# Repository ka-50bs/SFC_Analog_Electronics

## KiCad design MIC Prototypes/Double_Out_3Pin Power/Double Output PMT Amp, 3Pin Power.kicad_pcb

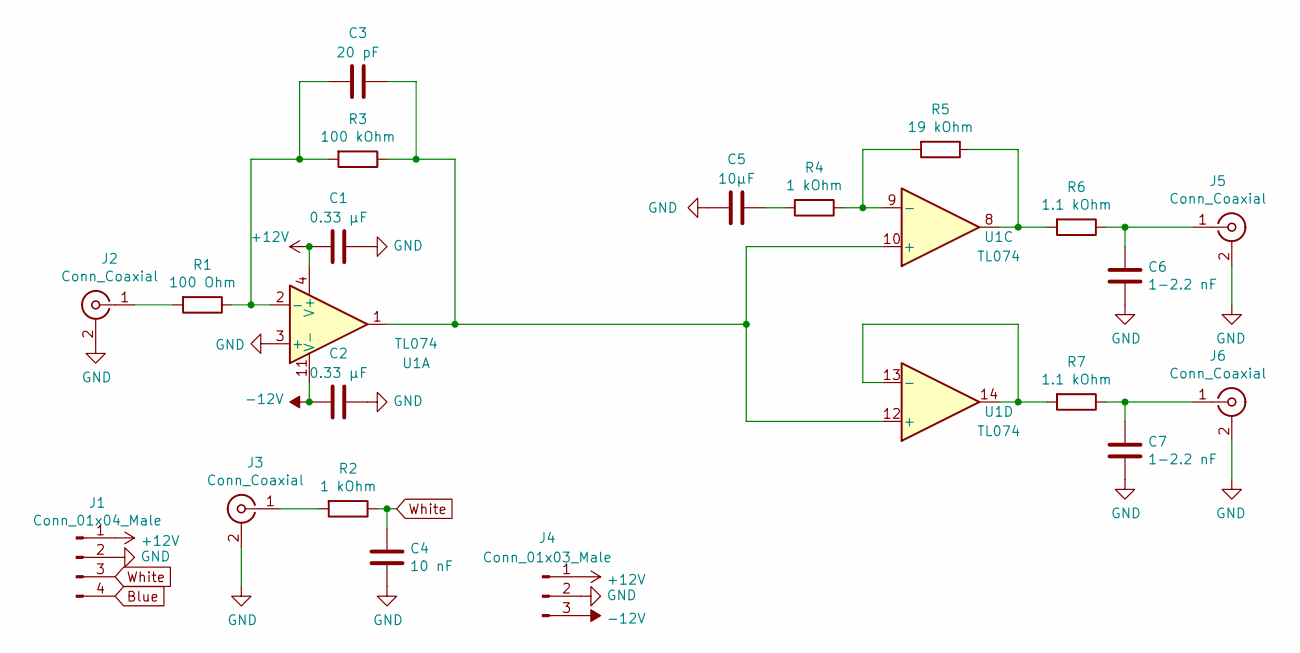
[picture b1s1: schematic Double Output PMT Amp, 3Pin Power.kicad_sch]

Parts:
C1, C2: 0.33 μF; C_1206_3216Metric_Pad1.33x1.80mm_HandSolder
C3: 20 pF; C_1206_3216Metric_Pad1.33x1.80mm_HandSolder
C4: 10 nF; C_1206_3216Metric_Pad1.33x1.80mm_HandSolder
C5: 10μF; C_1206_3216Metric_Pad1.33x1.80mm_HandSolder
C6, C7: 1-2.2 nF; C_1206_3216Metric_Pad1.33x1.80mm_HandSolder
J1: Conn_01x04_Male; PinHeader_1x04_P2.54mm_Vertical
J2, J3, J5, J6: Conn_Coaxial; SMA_Amphenol_132291-12_Vertical
J4: Conn_01x03_Male; Molex_KK-254_AE-6410-03A_1x03_P2.54mm_Vertical
R1: 100 Ohm; R_1206_3216Metric_Pad1.30x1.75mm_HandSolder
R2, R4: 1 kOhm; R_1206_3216Metric_Pad1.30x1.75mm_HandSolder
R3: 100 kOhm; R_1206_3216Metric_Pad1.30x1.75mm_HandSolder
R5: 19 kOhm; R_1206_3216Metric_Pad1.30x1.75mm_HandSolder
R6, R7: 1.1 kOhm; R_1206_3216Metric_Pad1.30x1.75mm_HandSolder
U1: TL074; DIP-14_W7.62mm_LongPads

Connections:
+12V: C1.2, J1.1, J4.1, U1.4 (V+)
-12V: C2.2, J4.3, U1.11 (V-)
Blue: J1.4
GND: C1.1, C2.1, C4.2, C5.1, C6.2, C7.2, J1.2, J2.2 (Ext), J3.2 (Ext), J4.2, J5.2 (Ext), J6.2 (Ext), U1.3 (+)
unnamed: C3.1, R3.1, U1.1, U1.10 (+), U1.12 (+)
unnamed: C3.2, R1.1, R3.2, U1.2 (-)
unnamed: C5.2, R4.2
unnamed: C6.1, J5.1 (In), R6.1
unnamed: C7.1, J6.1 (In), R7.1
unnamed: J2.1 (In), R1.2
unnamed: J3.1 (In), R2.2
unnamed: R4.1, R5.2, U1.9 (-)
unnamed: R5.1, R6.2, U1.8
unnamed: R7.2, U1.13 (-), U1.14
White: C4.1, J1.3, R2.1

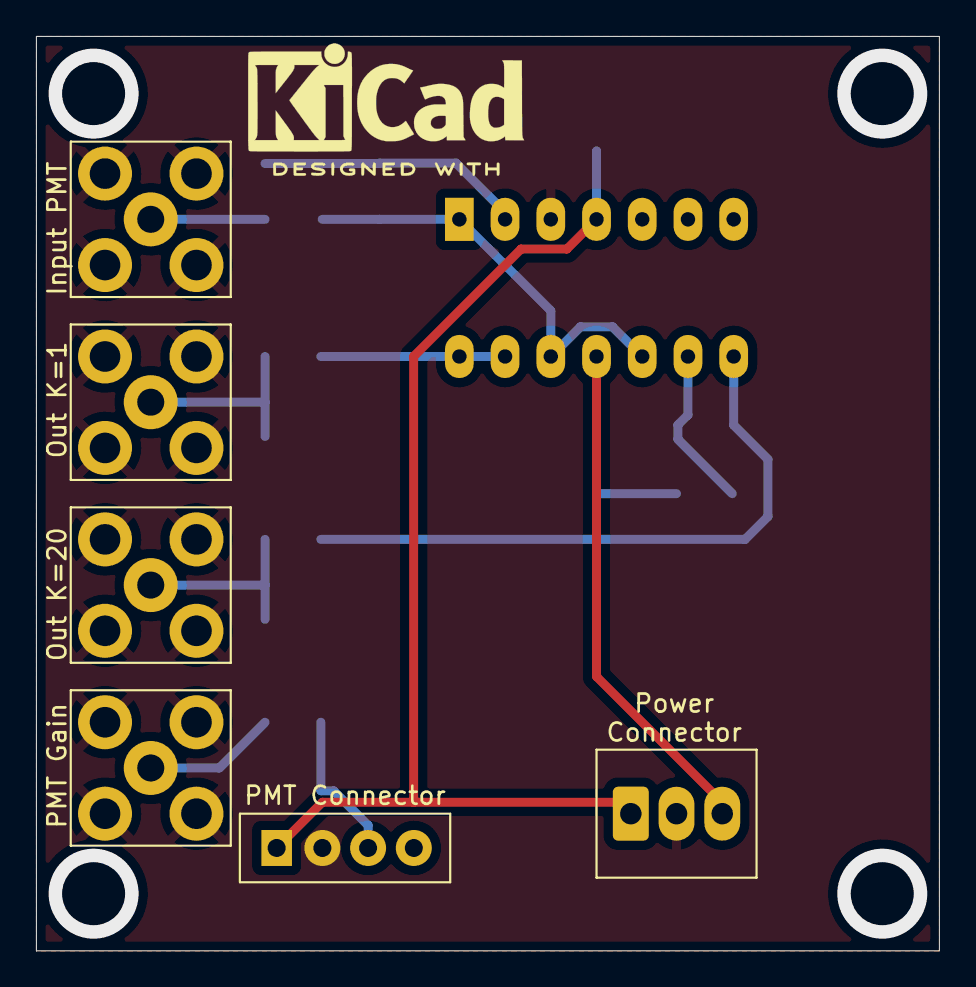
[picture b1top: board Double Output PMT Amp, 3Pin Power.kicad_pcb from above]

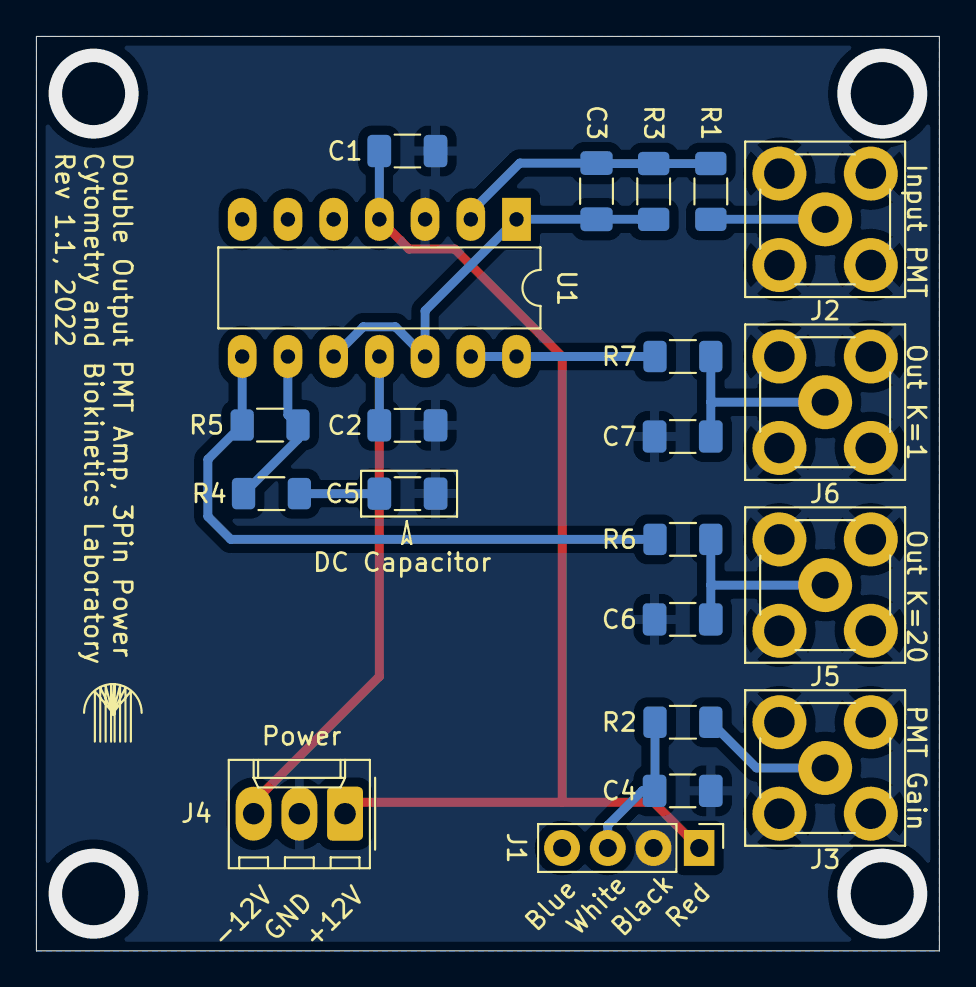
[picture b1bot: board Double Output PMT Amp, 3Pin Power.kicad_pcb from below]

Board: 2 copper layers, 50.2 x 50.8 mm, 21 parts (21 on the bottom side), 14 nets.

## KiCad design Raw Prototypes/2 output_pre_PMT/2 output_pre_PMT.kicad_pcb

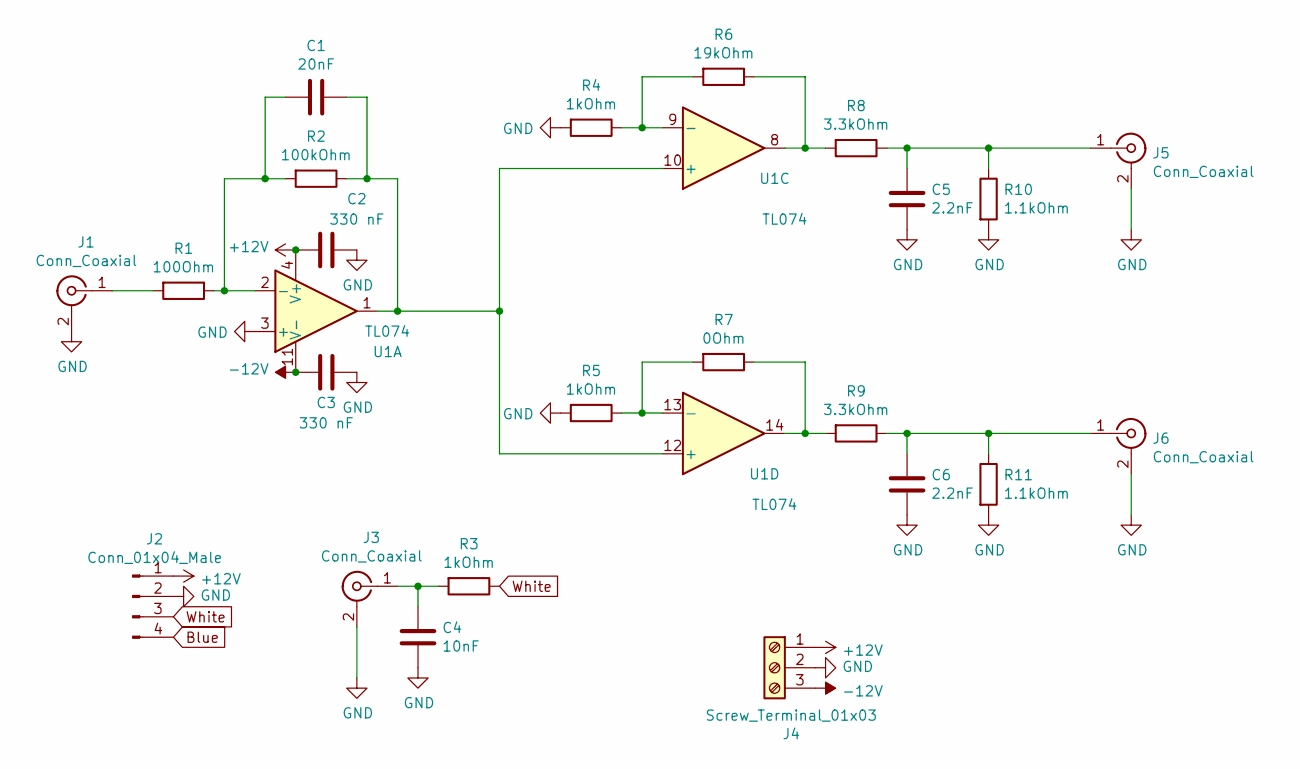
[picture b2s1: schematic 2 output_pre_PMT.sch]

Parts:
C1: 20nF; C_Disc_D7.5mm_W2.5mm_P5.00mm
C2, C3: 330 nF; C_Disc_D7.5mm_W2.5mm_P5.00mm
C4: 10nF; C_Disc_D7.5mm_W2.5mm_P5.00mm
C5, C6: 2.2nF; C_Disc_D7.5mm_W2.5mm_P5.00mm
J1, J3, J5, J6: Conn_Coaxial; SMA_Amphenol_132291-12_Vertical
J2: Conn_01x04_Male; PinHeader_1x04_P2.54mm_Vertical
J4: Screw_Terminal_01x03; TerminalBlock_Phoenix_MKDS-1,5-3_1x03_P5.00mm_Horizontal
R1: 100Ohm; R_Axial_DIN0207_L6.3mm_D2.5mm_P7.62mm_Horizontal
R2: 100kOhm; R_Axial_DIN0207_L6.3mm_D2.5mm_P7.62mm_Horizontal
R3, R4, R5: 1kOhm; R_Axial_DIN0207_L6.3mm_D2.5mm_P7.62mm_Horizontal
R6: 19kOhm; R_Axial_DIN0207_L6.3mm_D2.5mm_P7.62mm_Horizontal
R7: 0Ohm; R_Axial_DIN0207_L6.3mm_D2.5mm_P7.62mm_Horizontal
R8, R9: 3.3kOhm; R_Axial_DIN0207_L6.3mm_D2.5mm_P7.62mm_Horizontal
R10, R11: 1.1kOhm; R_Axial_DIN0207_L6.3mm_D2.5mm_P7.62mm_Horizontal
U1: TL074; DIP-14_W7.62mm_LongPads

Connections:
+12V: C2.2, J2.1, J4.1, U1.4 (V+)
-12V: C3.2, J4.3, U1.11 (V-)
Blue: J2.4
GND: C2.1, C3.1, C4.2, C5.2, C6.2, J1.2 (Ext), J2.2, J3.2 (Ext), J4.2, J5.2 (Ext), J6.2 (Ext), R4.2, R5.2, R10.2, R11.2, U1.3 (+)
unnamed: C1.1, R2.1, U1.1, U1.10 (+), U1.12 (+)
unnamed: C1.2, R1.1, R2.2, U1.2 (-)
unnamed: C4.1, J3.1 (In), R3.2
unnamed: C5.1, J5.1 (In), R8.1, R10.1
unnamed: C6.1, J6.1 (In), R9.1, R11.1
unnamed: J1.1 (In), R1.2
unnamed: R4.1, R6.2, U1.9 (-)
unnamed: R5.1, R7.2, U1.13 (-)
unnamed: R6.1, R8.2, U1.8
unnamed: R7.1, R9.2, U1.14
White: J2.3, R3.1

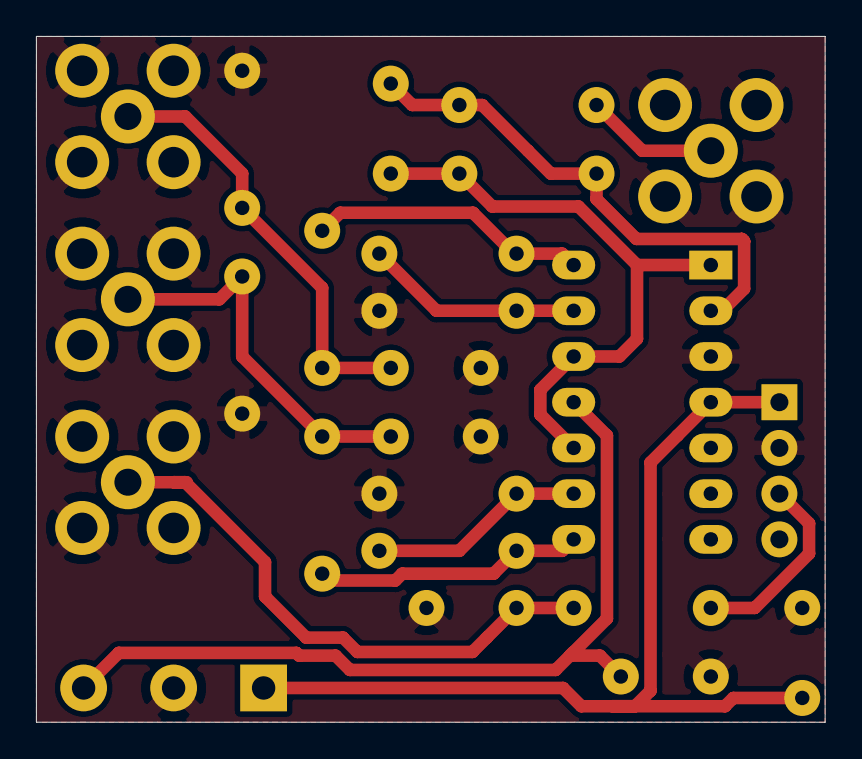
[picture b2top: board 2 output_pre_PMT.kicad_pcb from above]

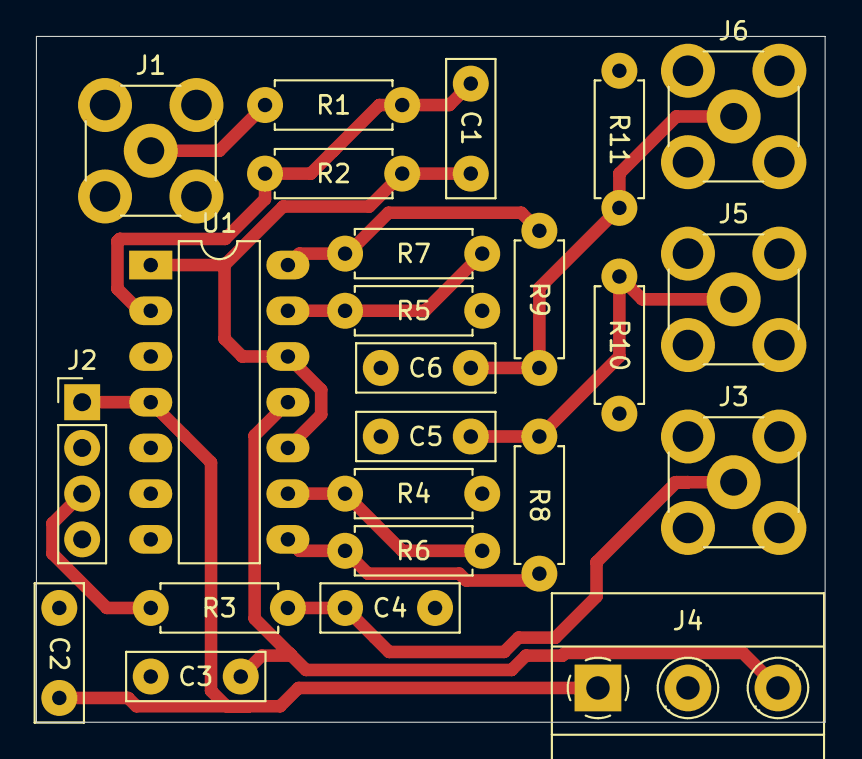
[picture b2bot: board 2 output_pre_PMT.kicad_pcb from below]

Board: 2 copper layers, 43.8 x 38.1 mm, 24 parts (24 on the bottom side), 14 nets.

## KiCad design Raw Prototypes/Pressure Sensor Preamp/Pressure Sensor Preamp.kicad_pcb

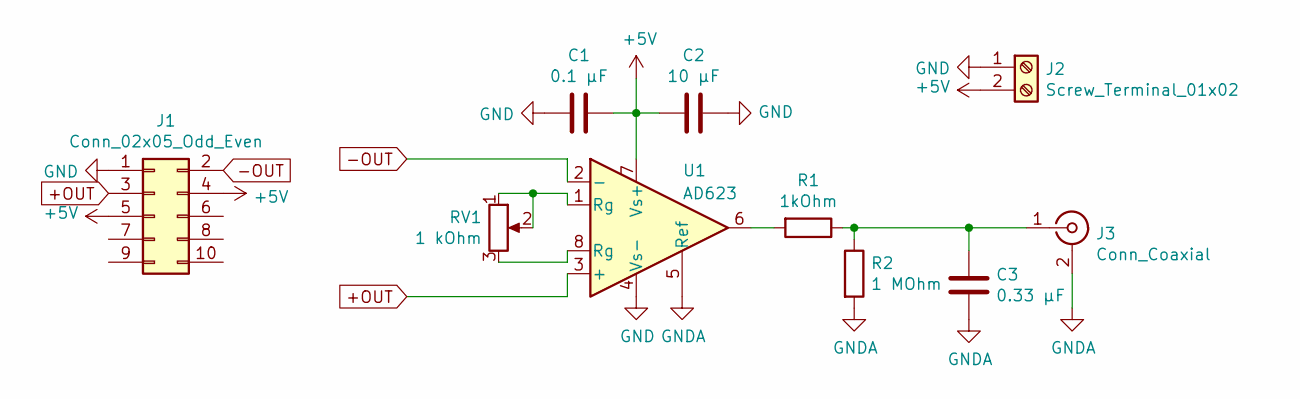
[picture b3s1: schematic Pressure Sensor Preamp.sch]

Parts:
C1: 0.1 μF; C_Disc_D9.0mm_W5.0mm_P7.50mm
C2: 10 μF; C_Disc_D9.0mm_W5.0mm_P7.50mm
C3: 0.33 μF; C_Disc_D9.0mm_W5.0mm_P7.50mm
J1: Conn_02x05_Odd_Even; IDC-Header_2x05_P2.54mm_Vertical
J2: Screw_Terminal_01x02; TerminalBlock_Phoenix_MKDS-1,5-2-5.08_1x02_P5.08mm_Horizont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
J3: Conn_Coaxial; SMA_Amphenol_132291-12_Vertical
R1: 1kOhm; R_Axial_DIN0207_L6.3mm_D2.5mm_P10.16mm_Horizontal
R2: 1 MOhm; R_Axial_DIN0207_L6.3mm_D2.5mm_P10.16mm_Horizontal
RV1: 1 kOhm; Potentiometer_Bourns_3266Y_Vertical
U1: AD623; DIP-8_W7.62mm_LongPads

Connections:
+5V: C1.1, C2.2, J1.4, J1.5, J2.2, U1.7 (Vs+)
+OUT: J1.3, U1.3 (+)
-OUT: J1.2, U1.2 (-)
GND: C1.2, C2.1, J1.1, J2.1, U1.4 (Vs-)
GNDA: C3.2, J3.2 (Ext), R2.2, U1.5 (Ref)
unnamed: C3.1, J3.1 (In), R1.1, R2.1
unnamed: R1.2, U1.6
unnamed: RV1.1, RV1.2, U1.1 (Rg)
unnamed: RV1.3, U1.8 (Rg)

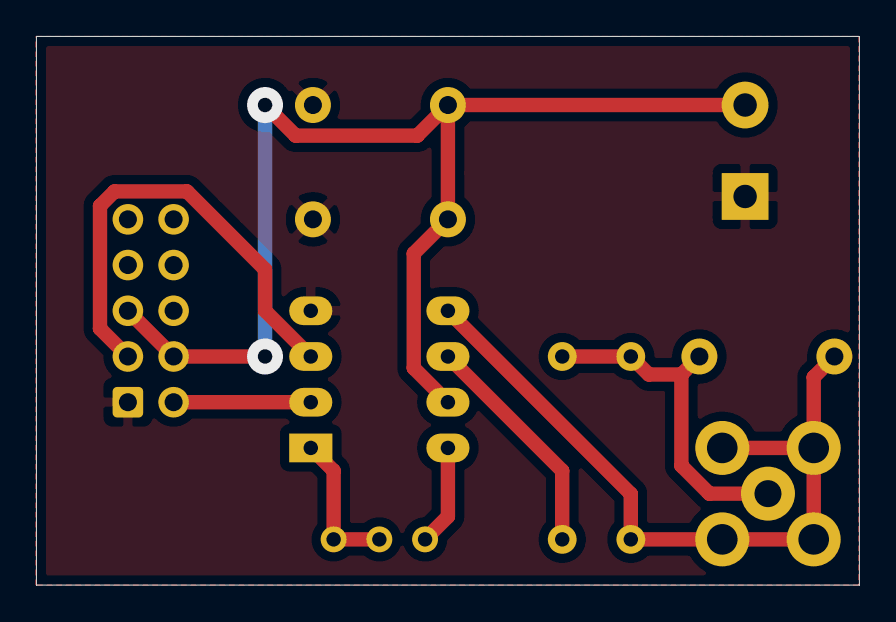
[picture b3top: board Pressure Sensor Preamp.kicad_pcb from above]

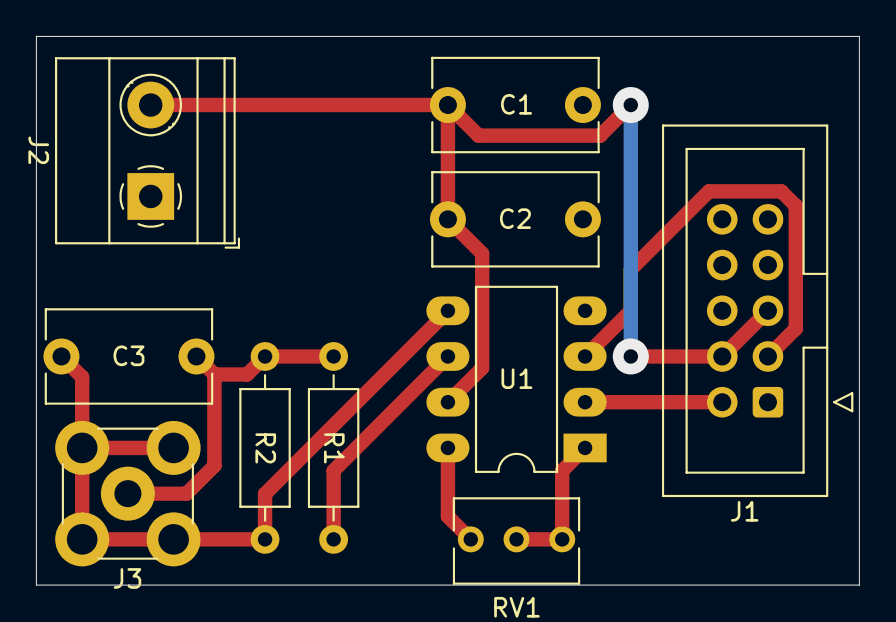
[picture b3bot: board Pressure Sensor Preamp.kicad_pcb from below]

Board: 2 copper layers, 45.7 x 30.5 mm, 10 parts (10 on the bottom side), 9 nets.

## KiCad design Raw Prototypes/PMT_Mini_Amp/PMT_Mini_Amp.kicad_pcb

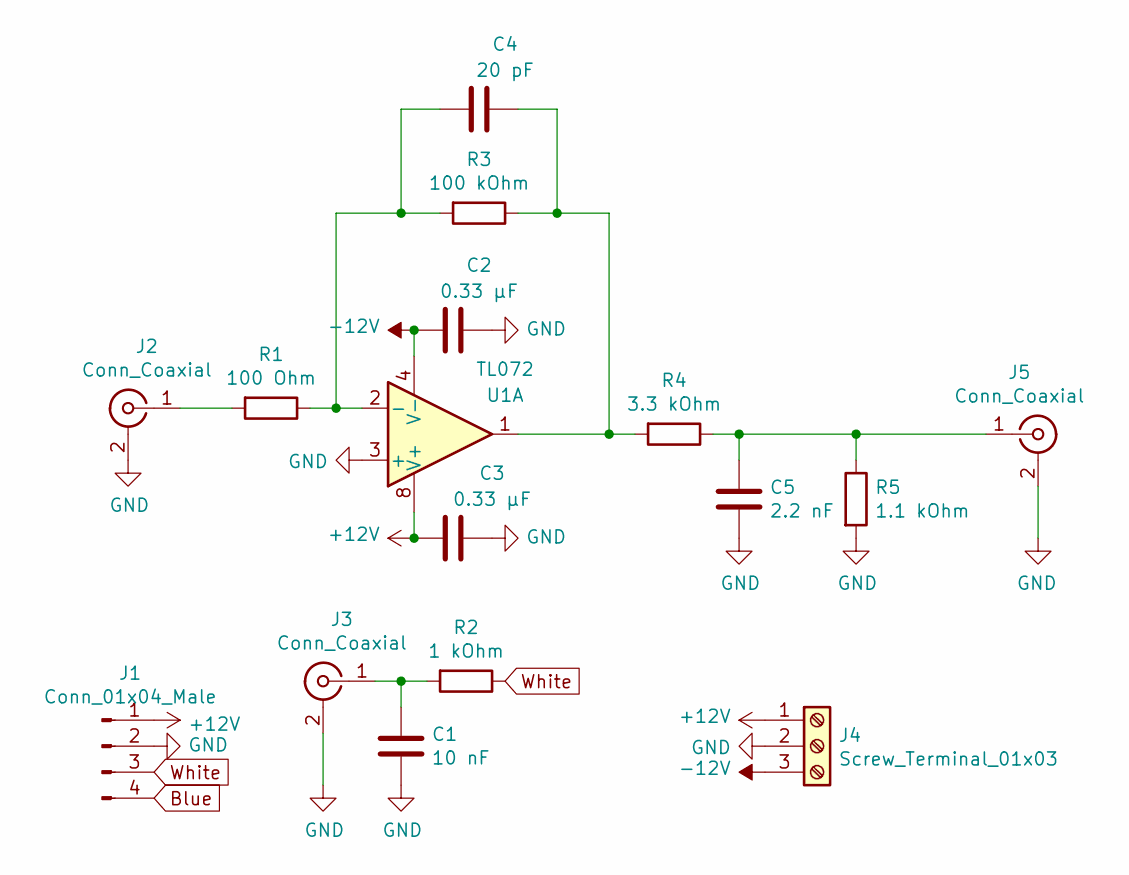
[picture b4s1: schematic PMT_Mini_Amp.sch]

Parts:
C1: 10 nF; C_Disc_D7.5mm_W5.0mm_P5.00mm
C2, C3: 0.33 μF; C_Disc_D7.5mm_W5.0mm_P5.00mm
C4: 20 pF; C_Disc_D7.5mm_W5.0mm_P5.00mm
C5: 2.2 nF; C_Disc_D7.5mm_W5.0mm_P5.00mm
J1: Conn_01x04_Male; PinHeader_1x04_P2.54mm_Horizontal
J2, J3, J5: Conn_Coaxial; SMA_Amphenol_132291-12_Vertical
J4: Screw_Terminal_01x03; TerminalBlock_Phoenix_MKDS-1,5-3-5.08_1x03_P5.08mm_Horizont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
R1: 100 Ohm; R_Axial_DIN0207_L6.3mm_D2.5mm_P10.16mm_Horizontal
R2: 1 kOhm; R_Axial_DIN0207_L6.3mm_D2.5mm_P10.16mm_Horizontal
R3: 100 kOhm; R_Axial_DIN0207_L6.3mm_D2.5mm_P10.16mm_Horizontal
R4: 3.3 kOhm; R_Axial_DIN0207_L6.3mm_D2.5mm_P10.16mm_Horizontal
R5: 1.1 kOhm; R_Axial_DIN0207_L6.3mm_D2.5mm_P10.16mm_Horizontal
U1: TL072; DIP-8_W7.62mm_LongPads

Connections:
+12V: C3.2, J1.1, J4.1, U1.8 (V+)
-12V: C2.2, J4.3, U1.4 (V-)
Blue: J1.4
GND: C1.2, C2.1, C3.1, C5.2, J1.2, J2.2 (Ext), J3.2 (Ext), J4.2, J5.2 (Ext), R5.2, U1.3 (+)
unnamed: C1.1, J3.1 (In), R2.2
unnamed: C4.1, R3.1, R4.2, U1.1
unnamed: C4.2, R1.1, R3.2, U1.2 (-)
unnamed: C5.1, J5.1 (In), R4.1, R5.1
unnamed: J2.1 (In), R1.2
White: J1.3, R2.1

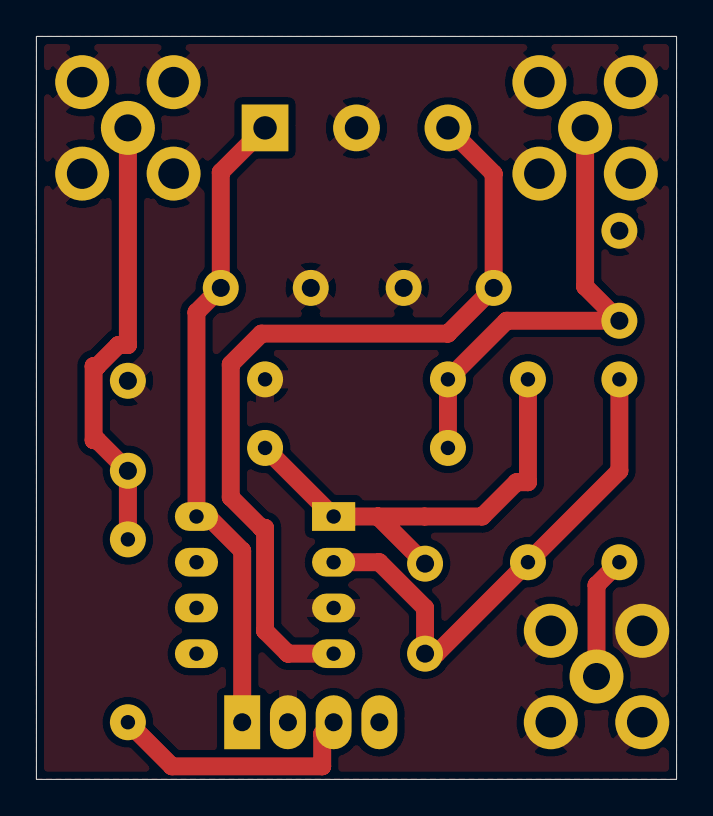
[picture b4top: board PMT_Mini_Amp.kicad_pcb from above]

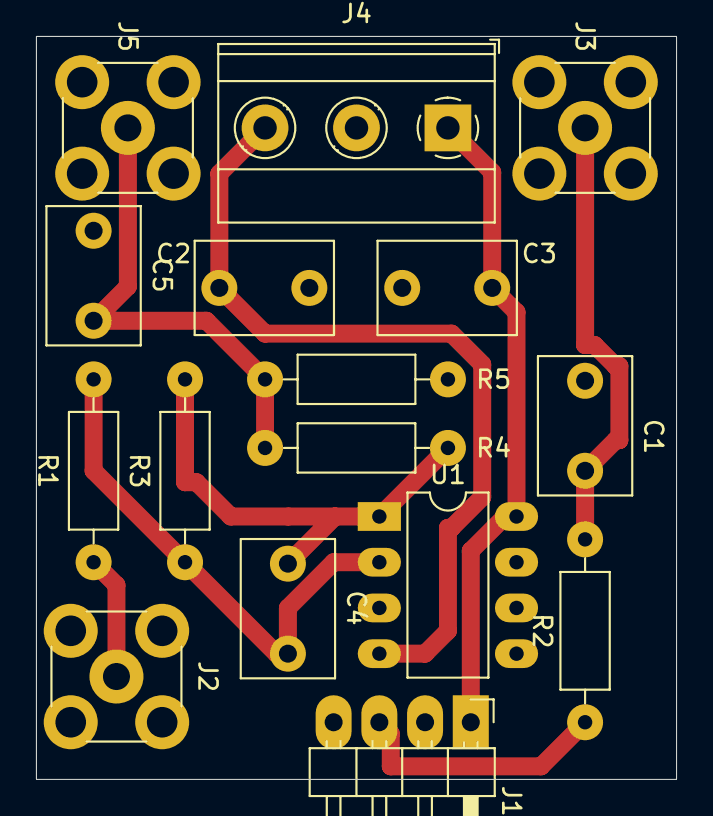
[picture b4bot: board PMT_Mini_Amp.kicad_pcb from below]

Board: 2 copper layers, 35.6 x 41.3 mm, 16 parts (16 on the bottom side), 9 nets.

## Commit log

2021-11-25 Added raw prototypes
2021-12-08 Added 2 output preamp
2023-02-27 Добавлено Block Scheme
2023-02-27 Обновление Block Scheme
